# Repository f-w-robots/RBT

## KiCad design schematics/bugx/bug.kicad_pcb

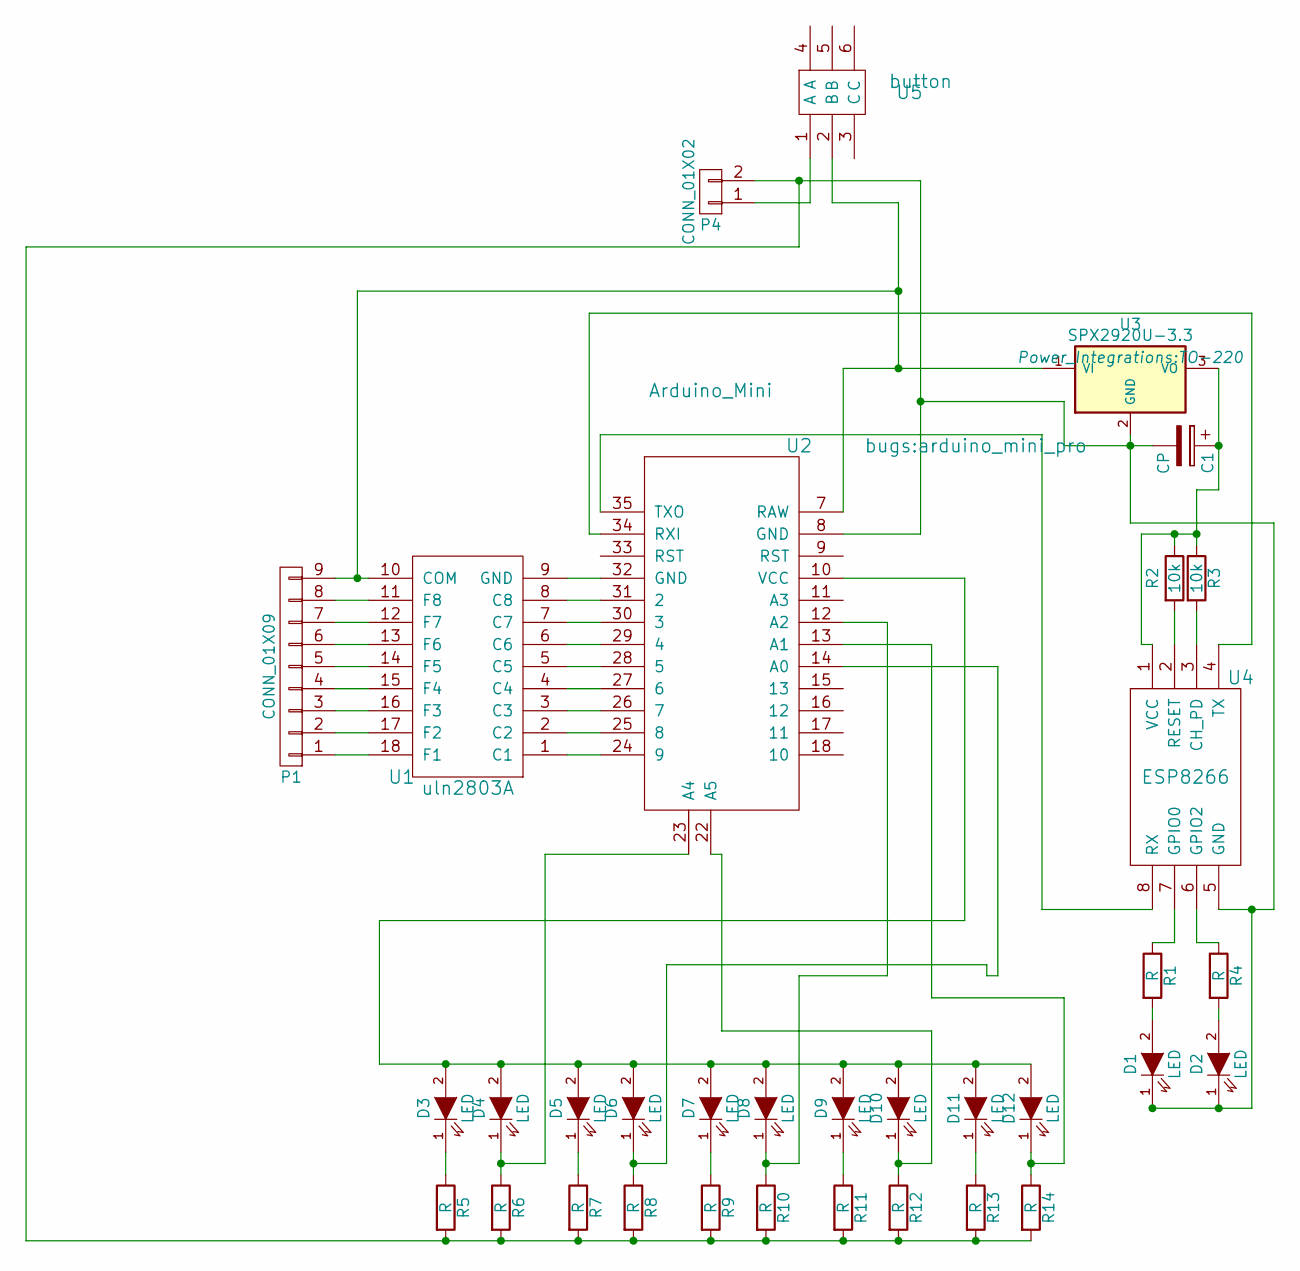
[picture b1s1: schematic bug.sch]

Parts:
C1: CP; CPR10X16
D1, D2: LED; LED-5MM
D3, D4, D5, D6, D7, D8, D9, D10, D11, D12: LED; LED-3MM
P1: CONN_01X09; Pin_Header_Straight_1x09
P4: CONN_01X02; Pin_Header_Straight_1x02
R1, R4, R5, R6, R7, R8, R9, R10, R11, R12, R13, R14: R; rc05_vert
R2, R3: 10k; rc05_vert
U1: uln2803A; DIP-18_W7.62mm
U2: Arduino_Mini; arduino_mini_pro
U3: SPX2920U-3.3; TO-220
U4: ESP8266
U5: button

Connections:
unnamed: C1.1, R2.1, R3.1, U3.3 (VO), U4.1 (VCC)
unnamed: C1.2, D1.1 (K), D2.1 (K), P4.2, R5.2, R6.2, R7.2, R8.2, R9.2, R10.2, R11.2, R12.2, R13.2, R14.2, U2.8 (GND), U3.2 (GND), U4.5 (GND)
unnamed: D1.2 (A), R1.2
unnamed: D2.2 (A), R4.2
unnamed: D3.1 (K), R5.1
unnamed: D4.1 (K), R6.1, U2.23 (A4)
unnamed: D5.1 (K), R7.1
unnamed: D6.1 (K), R8.1, U2.14 (A0)
unnamed: D7.1 (K), R9.1
unnamed: D8.1 (K), R10.1, U2.12 (A2)
unnamed: D9.1 (K), R11.1
unnamed: D10.1 (K), R12.1, U2.22 (A5)
unnamed: D3.2 (A), D4.2 (A), D5.2 (A), D6.2 (A), D7.2 (A), D8.2 (A), D9.2 (A), D10.2 (A), D11.2 (A), D12.2 (A), U2.10 (VCC)
unnamed: D11.1 (K), R13.1
unnamed: D12.1 (K), R14.1, U2.13 (A1)
unnamed: P1.1, U1.18 (F1)
unnamed: P1.2, U1.17 (F2)
unnamed: P1.3, U1.16 (F3)
unnamed: P1.4, U1.15 (F4)
unnamed: P1.5, U1.14 (F5)
unnamed: P1.6, U1.13 (F6)
unnamed: P1.7, U1.12 (F7)
unnamed: P1.8, U1.11 (F8)
unnamed: P1.9, U1.10 (COM), U2.7 (RAW), U3.1 (VI), U5.2 (B)
unnamed: P4.1, U5.1 (A)
unnamed: R1.1, U4.7 (GPIO0)
unnamed: R2.2, U4.2 (RESET)
unnamed: R3.2, U4.3 (CH_PD)
unnamed: R4.1, U4.6 (GPIO2)
unnamed: U1.1 (C1), U2.24 (9)
unnamed: U1.2 (С2), U2.25 (8)
unnamed: U1.3 (С3), U2.26 (7)
unnamed: U1.4 (С4), U2.27 (6)
unnamed: U1.5 (С5), U2.28 (5)
unnamed: U1.6 (С6), U2.29 (4)
unnamed: U1.7 (С7), U2.30 (3)
unnamed: U1.8 (С8), U2.31 (2)
unnamed: U1.9 (GND), U2.32 (GND)
unnamed: U2.34 (RXI), U4.4 (TX)
unnamed: U2.35 (TXO), U4.8 (RX)

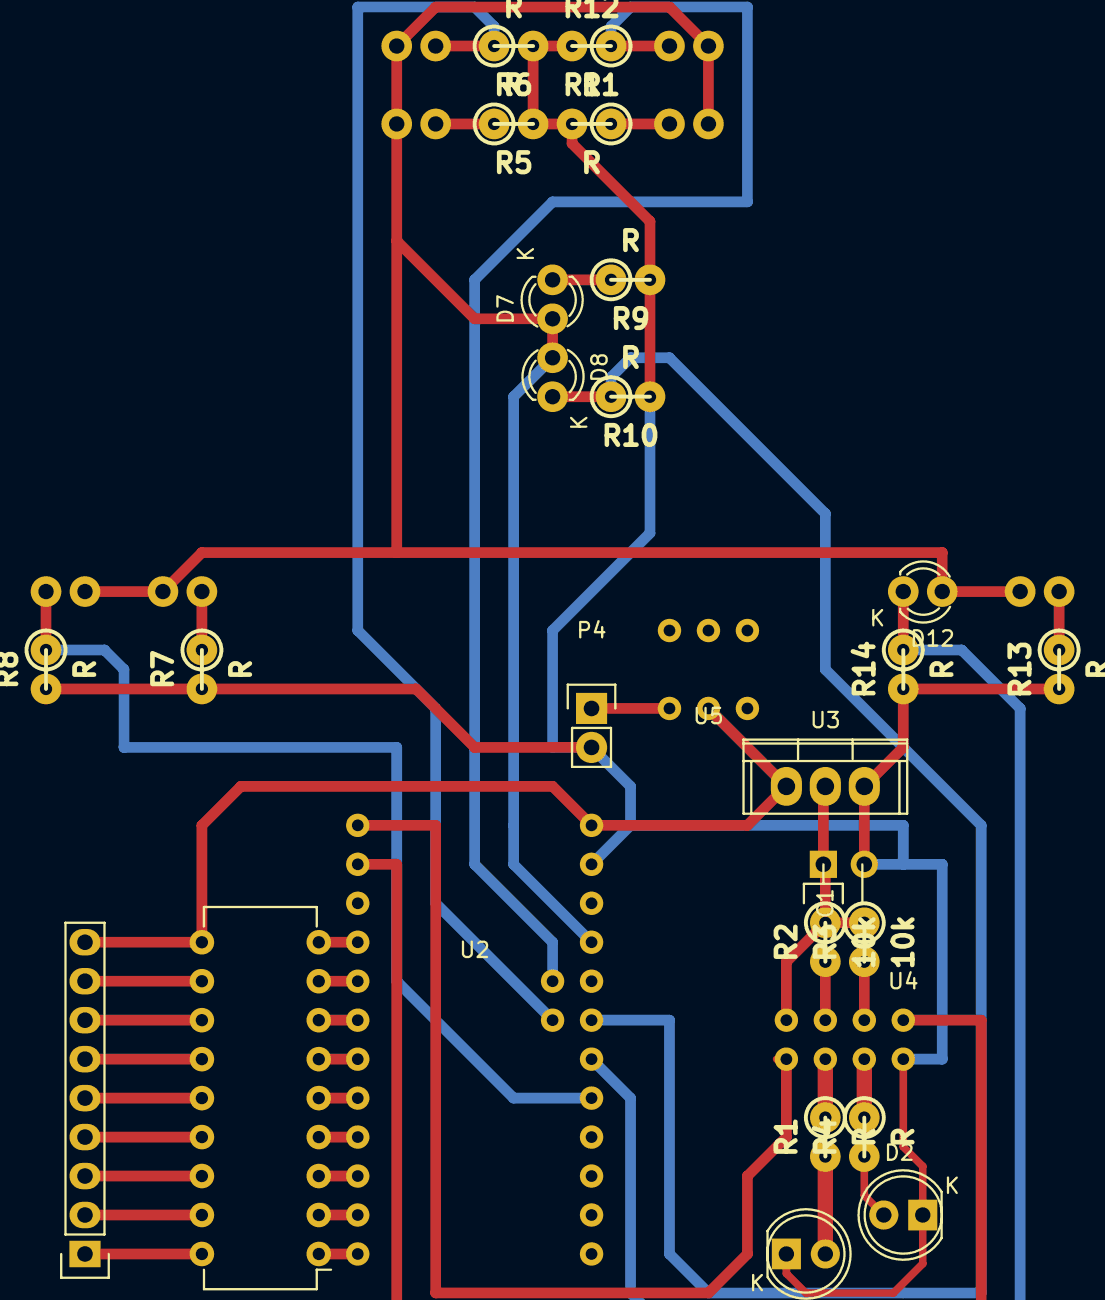
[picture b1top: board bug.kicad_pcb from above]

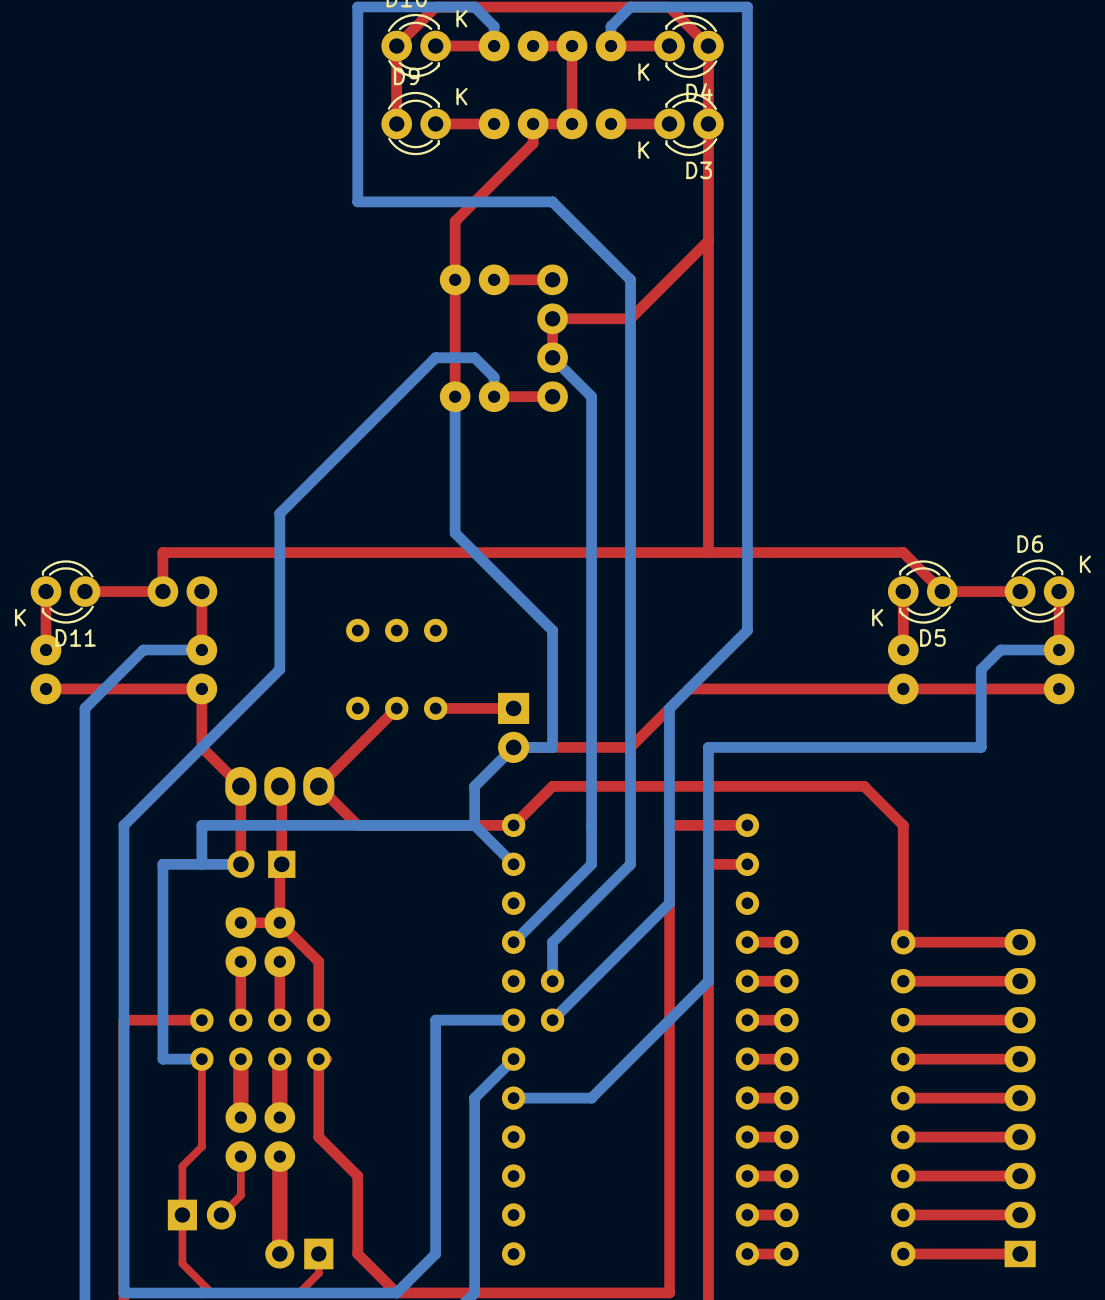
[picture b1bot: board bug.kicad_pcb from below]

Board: 2 copper layers, 34 parts (7 on the bottom side), 40 nets.

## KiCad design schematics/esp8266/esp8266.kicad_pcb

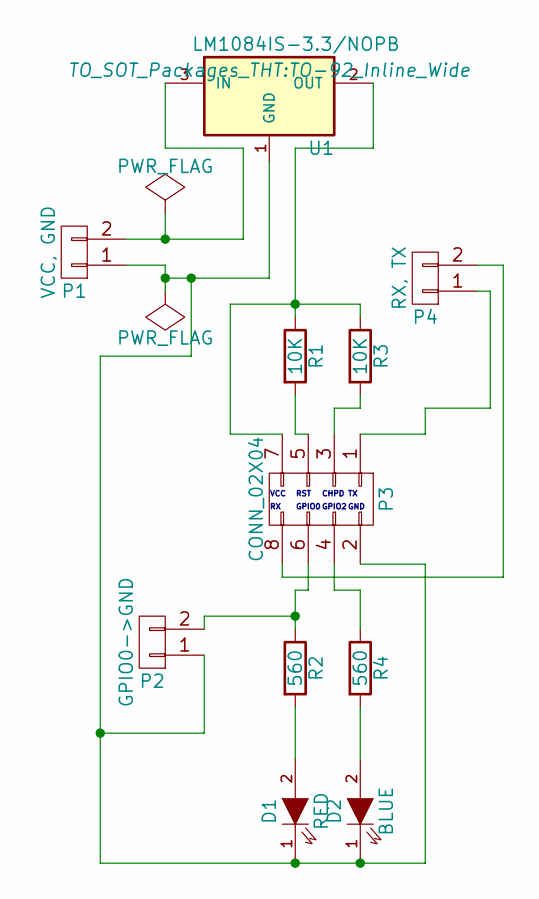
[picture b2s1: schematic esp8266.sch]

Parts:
D1: RED; LED-5MM
D2: BLUE; LED-5MM
P1: VCC, GND; Pin_Header_Straight_1x02
P2: GPIO0->GND; Pin_Header_Straight_1x02
P3: CONN_02X04; Pin_Header_Straight_2x04
P4: RX, TX; Pin_Header_Straight_1x02
R1, R3: 10K; rc05_vert
R2, R4: 560; RC05
U1: LM1084IS-3.3/NOPB; TO-92_Inline_Wide

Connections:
unnamed: D1.1 (K), D2.1 (K), P1.1, P2.1, P3.2, U1.1 (GND)
unnamed: D1.2 (A), R2.2
unnamed: D2.2 (A), R4.2
unnamed: P1.2, U1.3 (IN)
unnamed: P2.2, P3.6, R2.1
unnamed: P3.1, P4.1
unnamed: P3.3, R3.2
unnamed: P3.4, R4.1
unnamed: P3.5, R1.2
unnamed: P3.7, R1.1, R3.1, U1.2 (OUT)
unnamed: P3.8, P4.2

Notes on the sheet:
VCC
RST
CHPD
GPIO0
GPIO2
GND

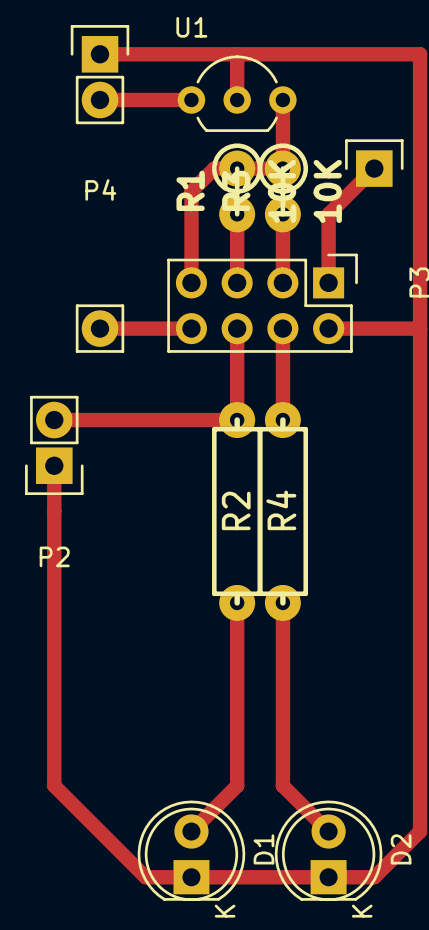
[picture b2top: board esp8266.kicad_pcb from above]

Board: 2 copper layers, 11 parts (0 on the bottom side), 11 nets.

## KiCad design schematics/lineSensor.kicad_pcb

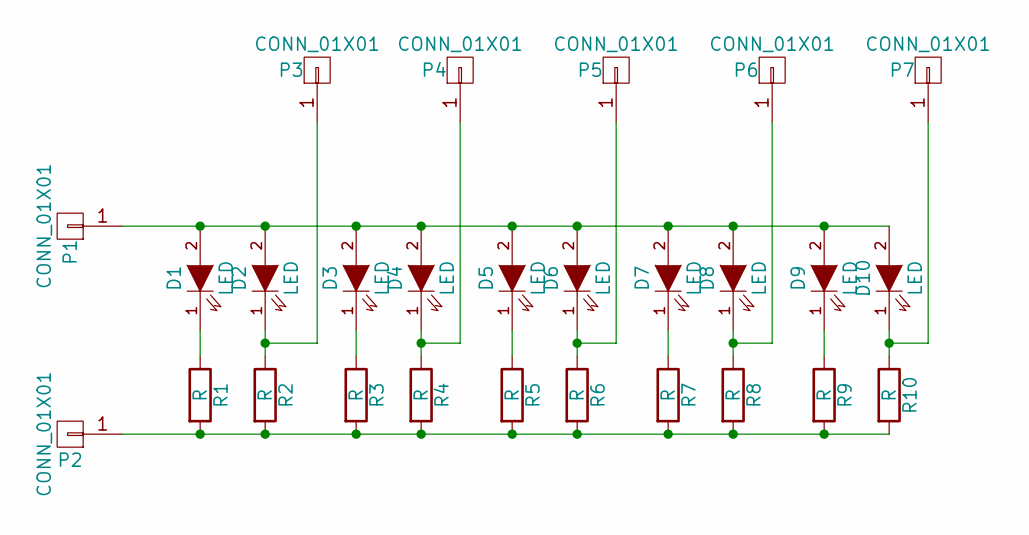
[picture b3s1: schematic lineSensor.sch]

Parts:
D1, D2, D3, D4, D5, D6, D7, D8, D9, D10: LED; LED-3MM
P1, P2, P3, P4, P5, P6, P7: CONN_01X01; Pin_Header_Straight_1x01
R1, R2, R3, R4, R5, R6, R7, R8, R9, R10: R; resistor2pins

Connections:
unnamed: D1.1 (K), R1.1
unnamed: D1.2 (A), D2.2 (A), D3.2 (A), D4.2 (A), D5.2 (A), D6.2 (A), D7.2 (A), D8.2 (A), D9.2 (A), D10.2 (A), P1.1
unnamed: D2.1 (K), P3.1, R2.1
unnamed: D3.1 (K), R3.1
unnamed: D4.1 (K), P4.1, R4.1
unnamed: D5.1 (K), R5.1
unnamed: D6.1 (K), P5.1, R6.1
unnamed: D7.1 (K), R7.1
unnamed: D8.1 (K), P6.1, R8.1
unnamed: D9.1 (K), R9.1
unnamed: D10.1 (K), P7.1, R10.1
unnamed: P2.1, R1.2, R2.2, R3.2, R4.2, R5.2, R6.2, R7.2, R8.2, R9.2, R10.2

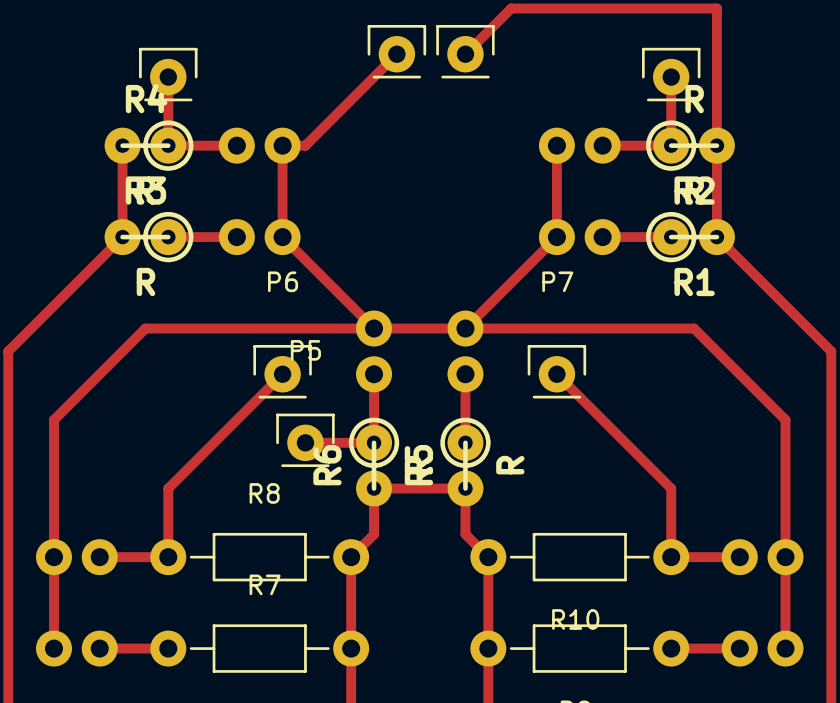
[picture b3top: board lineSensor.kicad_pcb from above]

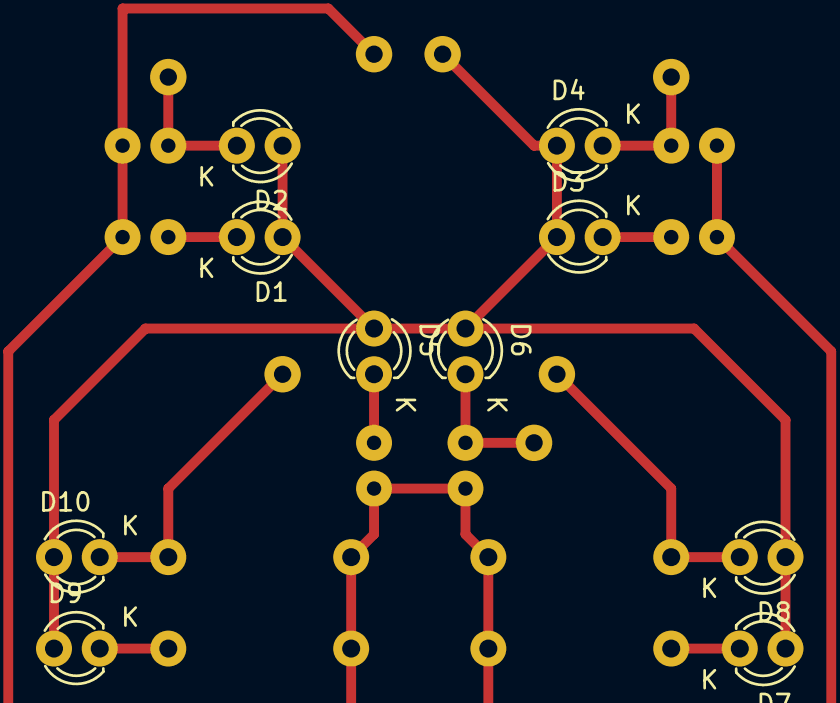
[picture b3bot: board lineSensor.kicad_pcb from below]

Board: 2 copper layers, 27 parts (10 on the bottom side), 12 nets.
